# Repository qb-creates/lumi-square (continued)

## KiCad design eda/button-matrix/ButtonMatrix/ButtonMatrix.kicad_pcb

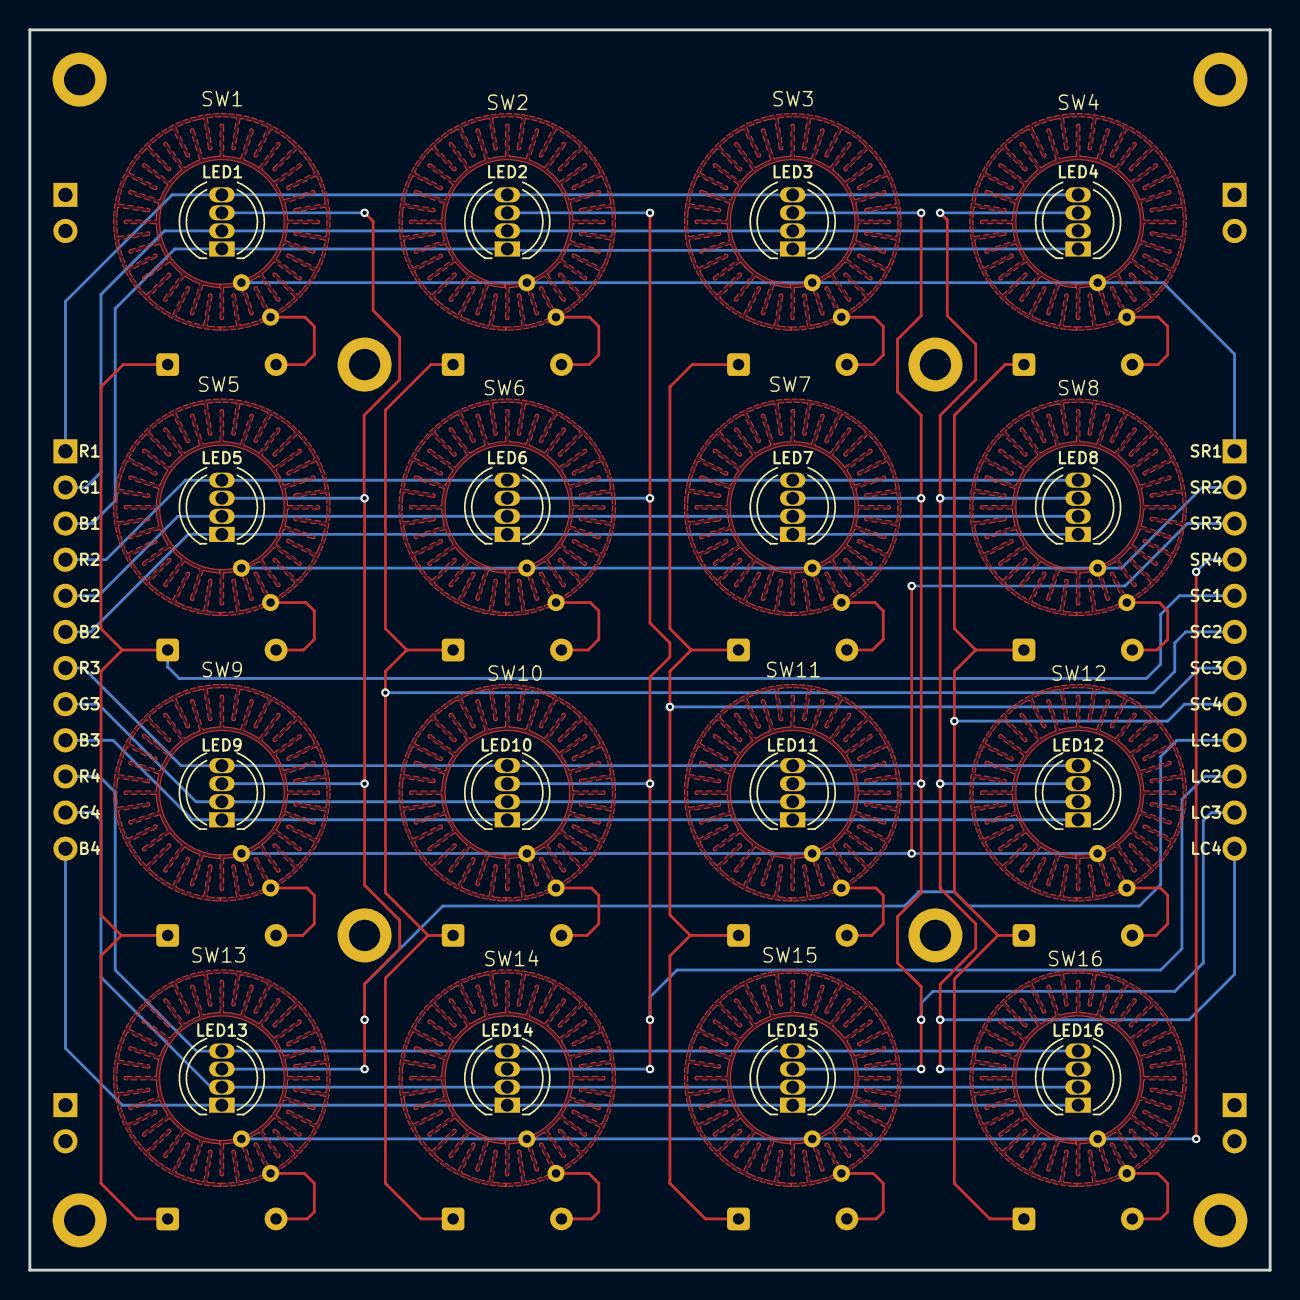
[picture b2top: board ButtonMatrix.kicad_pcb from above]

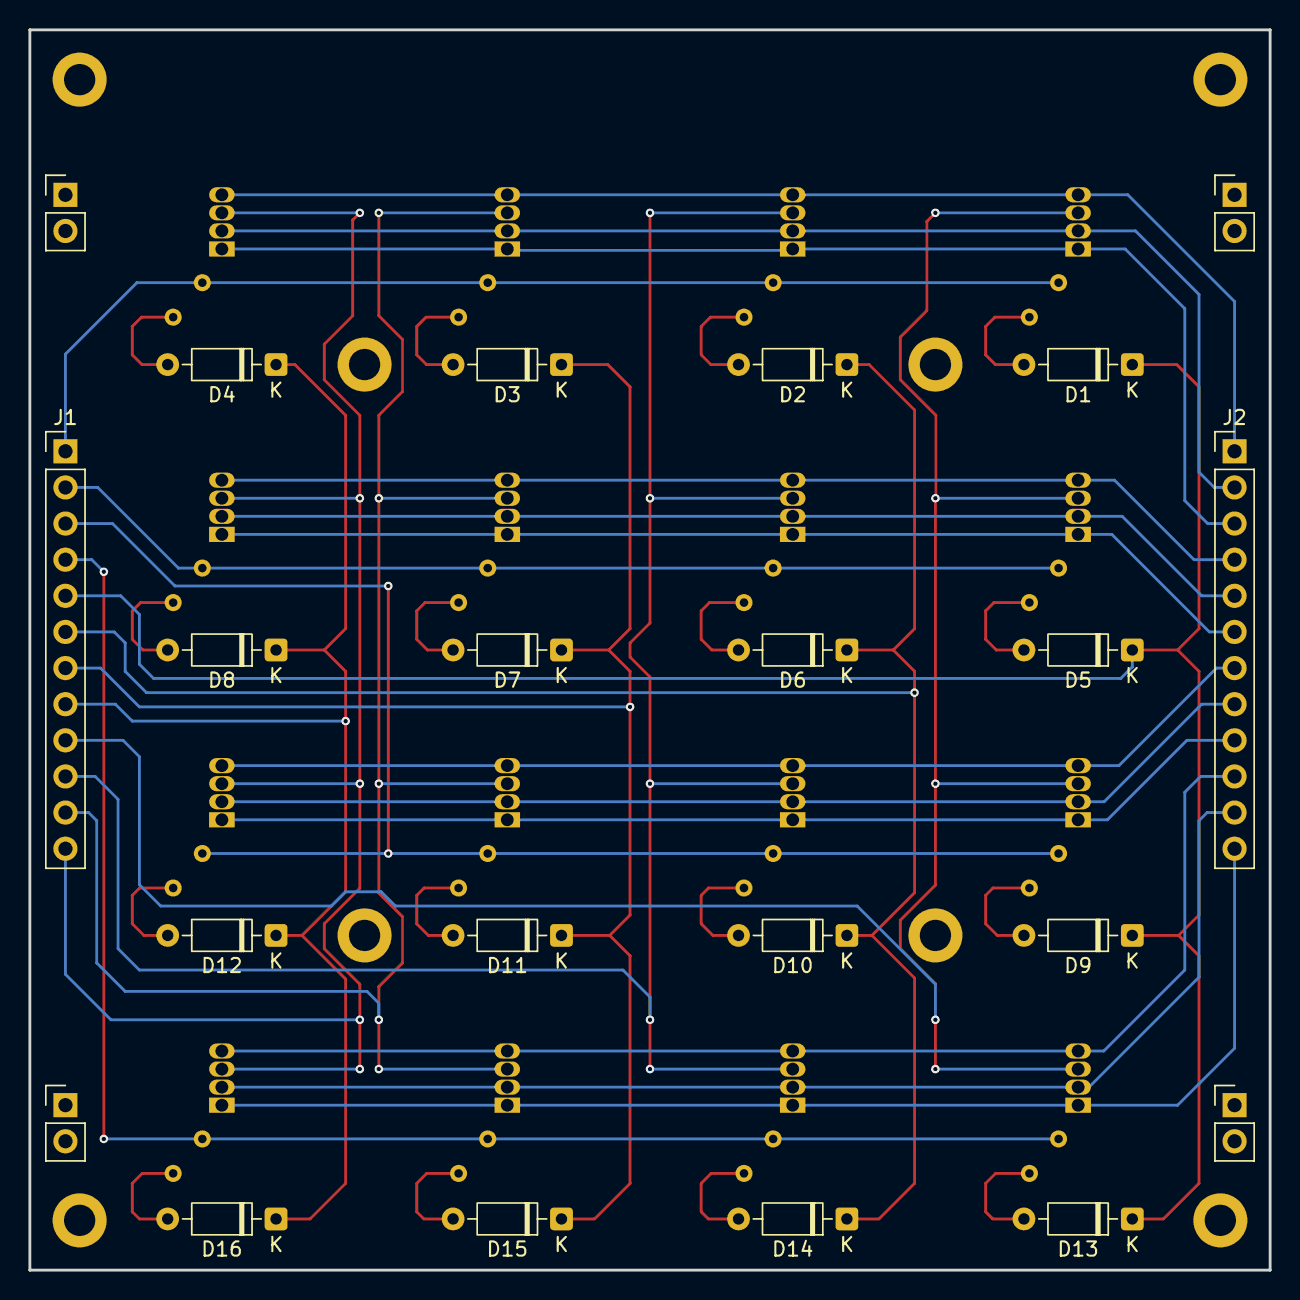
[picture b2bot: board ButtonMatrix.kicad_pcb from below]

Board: 2 copper layers, 87.2 x 87.2 mm, 50 parts (18 on the bottom side), 40 nets.

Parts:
D1, D2, D3, D4, D5, D6, D7, D8, D9, D10, D11, D12, D13, D14, D15, D16: 1N4148; D_DO-35_SOD27_P7.62mm_Horizontal
J1, J2: Conn_01x12; PinHeader_1x12_P2.54mm_Vertical
LED1, LED2, LED3, LED4, LED5, LED6, LED7, LED8, LED9, LED10, LED11, LED12, LED13, LED14, LED15, LED16: LED_BGAR; LED_D5.0mm-4_RGB
SW1, SW2, SW3, SW4, SW5, SW6, SW7, SW8, SW9, SW10, SW11, SW12, SW13, SW14, SW15, SW16: lumisquare button

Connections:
/LED_B1: J2.3, LED1.1 (BK), LED2.1 (BK), LED3.1 (BK), LED4.1 (BK)
/LED_B2: J2.6, LED5.1 (BK), LED6.1 (BK), LED7.1 (BK), LED8.1 (BK)
/LED_B3: J2.9, LED9.1 (BK), LED10.1 (BK), LED11.1 (BK), LED12.1 (BK)
/LED_B4: J2.12, LED13.1 (BK), LED14.1 (BK), LED15.1 (BK), LED16.1 (BK)
/LED_COL1: J1.9, LED1.3 (A), LED5.3 (A), LED9.3 (A), LED13.3 (A)
/LED_COL2: J1.10, LED2.3 (A), LED6.3 (A), LED10.3 (A), LED14.3 (A)
/LED_COL3: J1.11, LED3.3 (A), LED7.3 (A), LED11.3 (A), LED15.3 (A)
/LED_COL4: J1.12, LED4.3 (A), LED8.3 (A), LED12.3 (A), LED16.3 (A)
/LED_G1: J2.2, LED1.2 (GK), LED2.2 (GK), LED3.2 (GK), LED4.2 (GK)
/LED_G2: J2.5, LED5.2 (GK), LED6.2 (GK), LED7.2 (GK), LED8.2 (GK)
/LED_G3: J2.8, LED9.2 (GK), LED10.2 (GK), LED11.2 (GK), LED12.2 (GK)
/LED_G4: J2.11, LED13.2 (GK), LED14.2 (GK), LED15.2 (GK), LED16.2 (GK)
/LED_R1: J2.1, LED1.4 (RK), LED2.4 (RK), LED3.4 (RK), LED4.4 (RK)
/LED_R2: J2.4, LED5.4 (RK), LED6.4 (RK), LED7.4 (RK), LED8.4 (RK)
/LED_R3: J2.7, LED9.4 (RK), LED10.4 (RK), LED11.4 (RK), LED12.4 (RK)
/LED_R4: J2.10, LED13.4 (RK), LED14.4 (RK), LED15.4 (RK), LED16.4 (RK)
/SW_COL1: D1.1 (K), D5.1 (K), D9.1 (K), D13.1 (K), J1.5
/SW_COL2: D2.1 (K), D6.1 (K), D10.1 (K), D14.1 (K), J1.6
/SW_COL3: D3.1 (K), D7.1 (K), D11.1 (K), D15.1 (K), J1.7
/SW_COL4: D4.1 (K), D8.1 (K), D12.1 (K), D16.1 (K), J1.8
/SW_ROW1: J1.1, SW1.1, SW2.1, SW3.1, SW4.1
/SW_ROW2: J1.2, SW5.1, SW6.1, SW7.1, SW8.1
/SW_ROW3: J1.3, SW9.1, SW10.1, SW11.1, SW12.1
/SW_ROW4: J1.4, SW13.1, SW14.1, SW15.1, SW16.1
unnamed: D1.2 (A), SW1.2
unnamed: D2.2 (A), SW2.2
unnamed: D3.2 (A), SW3.2
unnamed: D4.2 (A), SW4.2
unnamed: D5.2 (A), SW5.2
unnamed: D6.2 (A), SW6.2
unnamed: D7.2 (A), SW7.2
unnamed: D8.2 (A), SW8.2
unnamed: D9.2 (A), SW9.2
unnamed: D10.2 (A), SW10.2
unnamed: D11.2 (A), SW11.2
unnamed: D12.2 (A), SW12.2
unnamed: D13.2 (A), SW13.2
unnamed: D14.2 (A), SW14.2
unnamed: D15.2 (A), SW15.2
unnamed: D16.2 (A), SW16.2

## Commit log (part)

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2023-07-19 Uploading the solution
2023-07-23 Updated animations and corrected state manager bugg
2023-07-24 - Added more notes to Audio.h - Removed tic tac toe - created simon cpp and header file - modified the game over state to play a game over animation - Added simon to state manager
2023-08-26 Created a class for managed lcd screen and added difficulty settings
2023-12-02 - Added a sleep feature to reduce power consumption - Return a bool from the scan button matrix funtion to reset the sleep timer. - Changed the PWM generation for audio from timer 1 to timer 3 - Fixe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
2023-12-03 - Refactored project to work with atmega1284 chip instead of atmega128
2024-02-10 Refactored the LCD class - Added cod docs and comments - Refactored teh writeNumber function to where it omit leading zeroes in a number. - Max number size is 3 digits
2024-02-11 Refactored the lightspeed st ate - Added an override for != to the Colors calss - Made a easy, medium, and hard dificulty for light speed - added a seed function the random class
2024-02-12 Added the ability to play music to the audio source class. - Added more notes to the MusicNote enum - Added a function that will loop through an array playing the notes for the specified time - Added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
2024-02-12 Modified the lcd class to where it can create custom characters - Created custom heart and low battery character - used hearts as the lives for simon game - Modified the audio in simon game.
2024-02-14 Refactored the simon state - Made it to where all of the simon lights are dimmly lit and get brighter when they are played in the sequence
2024-02-14 Changed the address of the custom heart character and low battery character
2024-02-14 Refactored the simon state - renamed variables
2024-02-18 - Refactored main menu and the leds class - Created a getLedIntensityFunction - Created LedOn and LedOff functions that take in an array of indexes
2024-02-18 - Added a set difficulty function to the GameProperties class
2024-02-18 - Refactored memory matching game - Created methods for specific functions in the memory matching state.
2024-02-18 - Refactored the simon state - Renamed variables so that they make more sense - Created reusable functions
2024-02-19 - Refactored simon state - Renamed variables in simon state - Added comments to simon state
2024-02-21 - Created a gameproperties class that holds information about the games - Created a high score manager that can save and retrieve high scores - Added a protected currentState constant to GameBaseStat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
2024-02-23 - Created a header file for music notes - created an audio clip class that can be used to play music and sound effects - Created a header file for sound effects - modified the audio source class to w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
2024-02-23 - fixed the value type in the writeNumber function
2024-02-23 - removed audio includes from state files and include aduio in the base state file - fixed bug with queued state being set to memory matching when the class is initialized - modified how the high sco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
2024-02-23 - Added a const high score init flag.
2024-02-24 - Renamed lightspeed to Light Dash - Updated light dash include patha and name change in state manager, high score manager, and game properties - Moved the GameProperties deleted copy constructor to 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
2024-02-24 - added a default leftAligned property to the writeNumber method.
2024-02-25 - Added a 3 second countdown timer before starting the selected game on the main menu state. - Refactored the clearDisplay function in the lcd class -
2024-03-09 - Added custom characters for easy, medium, and hard to lcd class
2024-03-10 - Added a mute function to th AudioSource class - Updated the pink and azure colors in hte colors.h header file
2024-03-10 - Modified the the fixed update ISR to where it is triggered every 250us. - Changed teh fixedUpdateCounter to 64 to still be a fixed update of 16ms - Changed _delay_us(2) to an assembly "NOP" call. -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
2024-03-10 - Added a color for blue to the Colors class - Updated the brightness for leds in the main menus state - Added a function to update highlighted button timer to the main menu - Added an update countdo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
2024-03-10 - Renamed the 'Buttons' directory to the 'Peripherals' directory.
2024-03-11 - Moved statemanger to the manager directory - made the sleep timer volatile - fixed issue with the colors include path in the leds header file - changed scanButtonMatrix to where it returns void ins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
2024-03-15 - Removed the clearSystemButtonStates function from the Input class - Cleared sleep button and mute button states in teh getMuteButtonDown() and getSleepButtonUp() functions
2024-03-15 - Created a fixed update class - Created a fixed event listener class - Made sleep manager and audio source singletons - Subscribed to the fixed update events
2024-03-23 - Uploading lumi-square bootloader
2024-04-01 - Refactored Light Dash - Modified lcd code to work with bjt driver circuit - Updated inlude file path in audio.cpp file.
2024-06-02 - Added a speaker and mute/unmute icon characters to the lcd - Updated the main menu to not overwrite the mute icon - updated teh main cpp to where it displays the mute icon. - Adjusted button bright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
2024-06-02 - Modified the bootloader to send a ctu acknowledgement to let the server know it is in bootloader mode and not running a program - Modified the bootloader to send a cts acknowledgement to let the se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
2024-06-02 - Removed sleep button code from sleep manager - Change inputs from sleep and mute to next and previous in the button class - Added code that will mute/unmute the audio if the previous and next butto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
2024-06-02 - added a boolean to check if the mute buttons are pressed or released to the audio source - added the ability to use the previous and next buttons to cycle through games in the main menu state - add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
2024-06-02 - Created a delta time const in the fixed update class - Added delta time constant to audio, game over state, light dash state, main menu state, matching state and sleep manager
2024-06-07 - Added another pushbutton for difficulty selection. PD7 - Modified the main menu state to where the difficulty push button increases the difficulty - Modified the audio class to where holding the di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
2024-06-16 - Removed sleep capabilities and instead sends a signal to the power controller to power down the device - Renamed sleepmanager to shutdownutility. - Renamed sleep variables and functions to reflect 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
2024-06-23 - Created a power on state - Added the power on state to the state dictionary in the state manager - Made power on state the default state in the state manager constructor - Added a PowerOn GameState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
2024-07-21 - Modified the LCD class to work with the SSD1306 oled - Commented out LCD non existing lcd functions used in light dash, main menu, and simon state. - Modified all of the states to use the new OLED 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
2025-03-29 - Added new voiceover manager - Removed lcd code as it is not being used anymore - Kecpt lcd scripts - Using usart1 for audio controls - Changed previous and next buttron from pd2 and pd3 to pc4 and 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
2025-03-30 - Added support for previousState to the basestate - Added a check to see if the game is memory dash before reading score.
2025-03-31 - Refactored files - Removed unnecessary header and cpp files
2025-03-31 - Refactored code - Updated file names and directories
2025-04-03 - Modified the bootloader to check for if the pin is low and return to the main program - Started the watchdog timer in the lumisquare code. - Do not reset watchdog timer if pc6 is high. Will allow u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
2025-04-27 - Changed the baud rate of the lumisquare bootloader to 9600 - Changed the bootloader to where it will check memory address 45 to see if it should enter the bootloader or jump to the application
2025-05-11 - Renamed audioClip functions and variables to musicNoteSequence - Modified the score manager to where it keeps track of all high scores. - Created a setHighScore function that can be used to save th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
2025-05-19 - Replaced all timer uint16_t timer variables with the Timer class - Created the serial command manager - MOved the usart PCINT initialization to the serial command manager - Moved the FixedUpdateEve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
2025-07-29 Removing atmega1284 lumisquare code
2025-07-29 Adding the samd21 lumisquare solution
2025-08-28 - Created a software directory and moved lumisquare projects into it
2025-08-28 - Adding the kicad project to the eda directory
2025-09-02 - Connected power portion of the schmatic - added components to the pcb editor
2025-10-17 Refactor device utilities and add desktop simulation support - Abstract DeviceUtility class with pure virtual methods for cross-platform support - Add SAMD21J18Utility concrete implementation for har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
2025-10-17 - Made updates to LumiSquare pcb and schematic
2025-10-19 Abstracted more hardware logic to the device utility class - abstracted led and rng hardware logic to the device utility class - Renamed the outputs class to LEDMatrix - put the LED class in its own 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
2025-10-20 - Moved rng seed hardware logic to the device utility
2025-10-21 - Abstracted dfplayer mini hardware code to the device utility
2025-10-22 - Abstracted beep notes to the device utility
2025-11-02 Adding button matrix kicad project- - Used dma to send audio usart data for samd21
2025-11-02 - Updated mesh button connections
2025-11-06 - Updated the pcb for the new 4x4 button matrix - Added support imgui and desktop support
2025-11-07 - Updates to button matrix pcb
2025-11-08 - Added m2 mounting holes to the pcb
2025-11-09 - Added headers and connected all diods
2025-11-09 - Updated PCB more
2025-11-09 - Connected led grounds
2025-11-10 - Fixed issue in my lumisquare button footrprint - Redesign teh button fill areas to better alingn witht he button mask
2025-11-10 - Fixed silk screen overlap issuess in button pcb
2025-11-10 - Completed all connections on pcb and performed design fule check
2025-11-10 - Added rgb silkscreens to label header pins.
2025-11-10 - Added more silkscreens to label switch headers
2025-11-13 - Added gerber files for button matrix - Added miniaudio to the project - Modified the desktopUtility to utilize miniaudio to play audio
2025-11-16 - Added a random seed to the desktoputility - Added an on audio complete callback to the desktoputility
2025-11-16 - Fixed bug with not being able to close using the x button. - Removed text labels from buttons - Updated my fixedUpdatethread function to where it properly sleeps the configured time.
2025-11-16 - Changed the build generator for my desktop utility to Ninja to speed it up. - Addded color diagnostics to build output
2025-11-17 - UKpdated desktop and standard cmake list to only include what each specific hardware needs - Created a new Desktop and SAMD21 directory in the Utilities directory. - Updated c_cpp_properties to inc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
2026-05-23 - uploading kicad pcb changes
2026-05-26 - Removed unnecessary colors and settled on just 8 - Updated teh samd21j18utility to work with the new p channel mosfets
2026-05-26 -Added circuity for esd on usb. - Add p chanel mosfets. - added new footprint, symbol, and step files
2026-05-26 Remove Windows Zone.Identifier file
2026-05-26 Remove Window Zone.Identifier file
2026-05-26 - Adding zone identifier to gitignore
2026-05-31 Adding updateds to pcb and schematic design
2026-06-01 Made more progress with the pcb layout
2026-06-02 Made more progress on the pcb
2026-06-06 Removed usb connection components and finished circuit
2026-06-07 Fixed warnings
2026-06-10 Fixed header positions
2026-06-15 Added test points
